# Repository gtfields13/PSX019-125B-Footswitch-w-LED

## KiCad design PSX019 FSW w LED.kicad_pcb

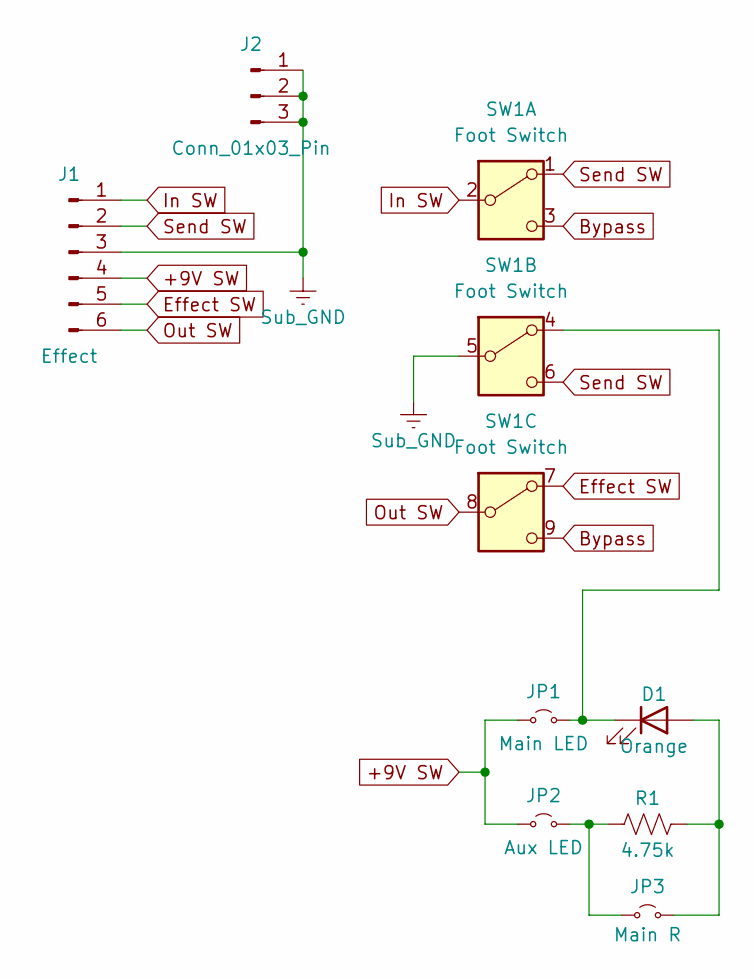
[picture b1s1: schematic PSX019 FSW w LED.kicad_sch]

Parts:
D1: Orange; LED_D5.0mm
J1: Effect; JST_PH_B6B-PH-K_1x06_P2.00mm_Vertical
J2: Conn_01x03_Pin; JST_XH_B3B-XH-AM_1x03_P2.50mm_Vertical
JP1: Main LED; JUMPER_SMD_1x2
JP2: Aux LED; JUMPER_SMD_1x2
JP3: Main R; JUMPER_SMD_1x2
R1: 4.75k; R_Axial_DIN0204_L3.6mm_D1.6mm_P7.62mm_Horizontal
SW1: Foot Switch; Switch

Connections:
+9V SW: J1.4, JP1.1 (A), JP2.1 (A)
Bypass: SW1.3 (C), SW1.9 (C)
Effect SW: J1.5, SW1.7 (A)
In SW: J1.1, SW1.2 (B)
unnamed: D1.2 (A), JP3.2 (B), R1.2
unnamed: D1.1 (K), JP1.2 (B), SW1.4 (A)
unnamed: JP2.2 (B), JP3.1 (A), R1.1
Out SW: J1.6, SW1.8 (B)
Send SW: J1.2, SW1.1 (A), SW1.6 (C)
Sub_GND: J1.3, J2.1, J2.2, J2.3, SW1.5 (B)

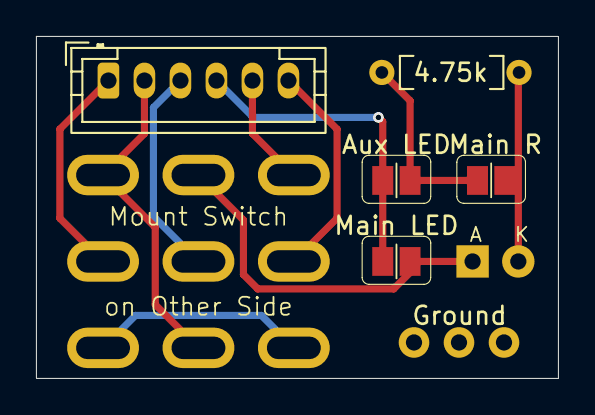
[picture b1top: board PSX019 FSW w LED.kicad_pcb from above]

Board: 2 copper layers, 29.0 x 19.0 mm, 8 parts (1 on the bottom side), 10 nets.
